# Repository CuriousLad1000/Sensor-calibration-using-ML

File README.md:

# Sensor calibration using Machine Learning

## Introduction

This repository presents one of the projects I built during the start of
the COVID-19 pandemic when there was a severe shortage of medical
equipment. Even something simple as a thermometer was either not
available or too costly to purchase. In this project, I used some
consumer-grade temperature sensors and calibrated them to provide
medical-grade precision and accuracy.

## Project Objective

The objective is to calibrate a commonly available temperature sensor to
provide medical grade accuracy. The sensor is calibrated by taking
readings from multiple medical grade thermometers as a benchmark and
then averaging them out.

The reading taken from thermometer and the sensor being calibrated are
then fit to a regression model to increase sensor's accuracy.

The model is then uploaded to the controller and after interfacing with
sensors and peripherals required, it produces accurate results under
calibrated range of a clinical thermometer (94-108 degrees F).

*Full list of features and capabilities are listed in a separate section below.*

## Hardware used

-   Arduino nano/pro min

-   3D printer casing for the temperature gun

-   Bright OLED display

-   battery

-   Laser pointer

-   Contactless Temperature sensor

-   Custom-built calibration heat bed

-   Clinical thermometers

-   Precision temperature sensors for heat-bed and reference

## Software used

-   Arduino IDE (C/C++ Programming)

-   Excel for data collection and regression model

-   GIMP for UI designing

-   Eagle for PCB designing

-   Fritzing for prototyping wiring diagram

## Features offered

-   Calibrated contactless temperature sensor.

-   Power-saving mode.

-   Inbuilt rechargeable batteries.

-   Temperature range similar to clinical thermometer.

-   Bright OLED display with easy-to-read readouts.

## Device pics

**Device**

<br/>

<br/>
<br/>

**Calibration setup <i>(gotta work with whatever you have during pandemic... this is a makeshift Heatbed PID controlled)</i>**

<br/>

<br/>
<br/>

<br/>

<br/>
<br/>

**Circuit board**

<br/>

<br/>
<br/>

**Calibration process**

<br/>

<br/>
<br/>

**UI Testing**

<br/>

<br/>
<br/>

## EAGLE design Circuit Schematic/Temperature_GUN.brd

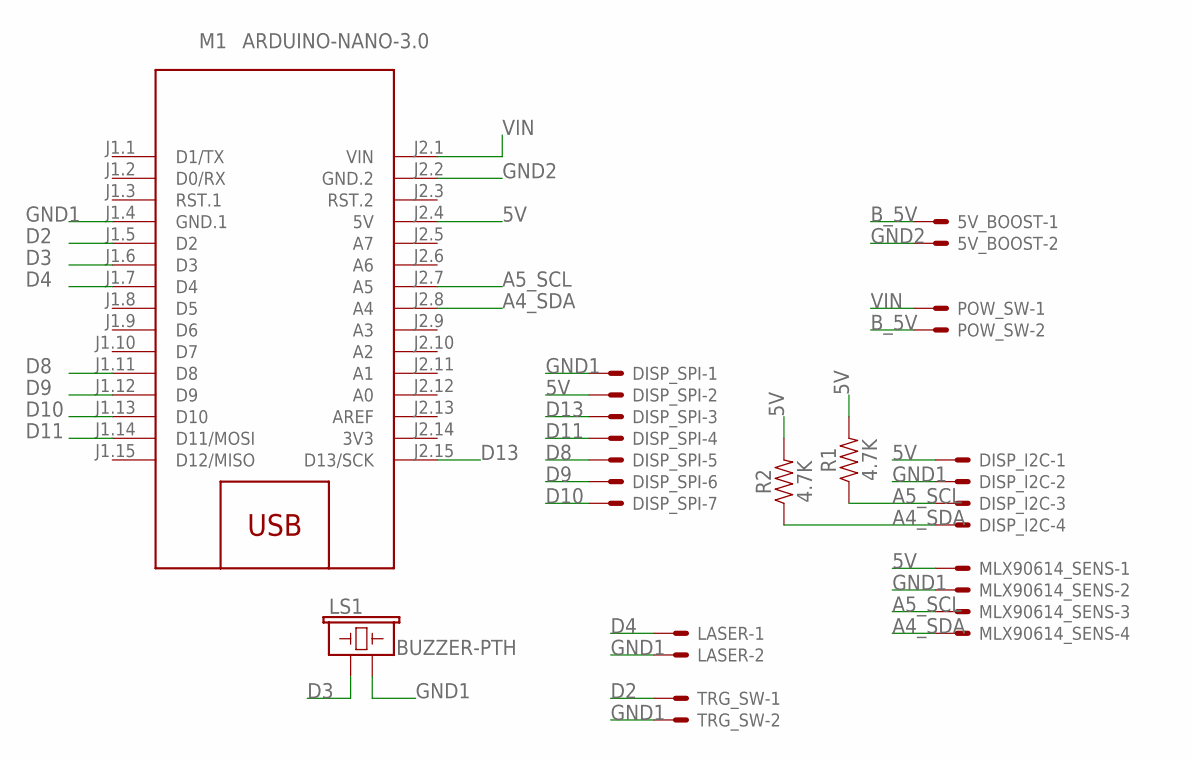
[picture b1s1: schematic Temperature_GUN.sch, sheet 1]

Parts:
5V_BOOST: JST-XH-02-PIN-ROUND-PAD; JST-XH-02-PACKAGE-ROUND-PAD
DISP_I2C: JST-XH-04-PIN-ROUND-PAD; JST-XH-04-PACKAGE-ROUND-PAD
DISP_SPI: JST-XH-07-PIN-ROUND-PAD; JST-XH-07-PACKAGE-ROUND-PAD
LASER: JST-XH-02-PIN-ROUND-PAD; JST-XH-02-PACKAGE-ROUND-PAD
LS1: BUZZER-PTH; BUZZER-12MM
M1: ARDUINO-NANO-3.0
MLX90614_SENS: JST-XH-04-PIN-ROUND-PAD; JST-XH-04-PACKAGE-ROUND-PAD
POW_SW: JST-XH-02-PIN-ROUND-PAD; JST-XH-02-PACKAGE-ROUND-PAD
R1, R2: 4.7K; AXIAL-0.3
TRG_SW: JST-XH-02-PIN-ROUND-PAD; JST-XH-02-PACKAGE-ROUND-PAD

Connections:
3V3: M1.J2.14 (3V3)
5V: DISP_I2C.1, DISP_SPI.2, M1.J2.4 (5V), MLX90614_SENS.1, R1.P$2 (2), R2.P$2 (2)
A4_SDA: DISP_I2C.4, M1.J2.8 (A4), MLX90614_SENS.4, R2.P$1 (1)
A5_SCL: DISP_I2C.3, M1.J2.7 (A5), MLX90614_SENS.3, R1.P$1 (1)
B_5V: 5V_BOOST.1, POW_SW.2
D2: M1.J1.5 (D2), TRG_SW.1
D3: LS1.+ (1), M1.J1.6 (D3)
D4: LASER.1, M1.J1.7 (D4)
D8: DISP_SPI.5, M1.J1.11 (D8)
D9: DISP_SPI.6, M1.J1.12 (D9)
D10: DISP_SPI.7, M1.J1.13 (D10)
D11: DISP_SPI.4, M1.J1.14 (D11/MOSI)
D13: DISP_SPI.3, M1.J2.15 (D13/SCK)
GND1: DISP_I2C.2, DISP_SPI.1, LASER.2, LS1.- (2), M1.J1.4 (GND.1), MLX90614_SENS.2, TRG_SW.2
GND2: 5V_BOOST.2, M1.J2.2 (GND.2)
VIN: M1.J2.1 (VIN), POW_SW.1

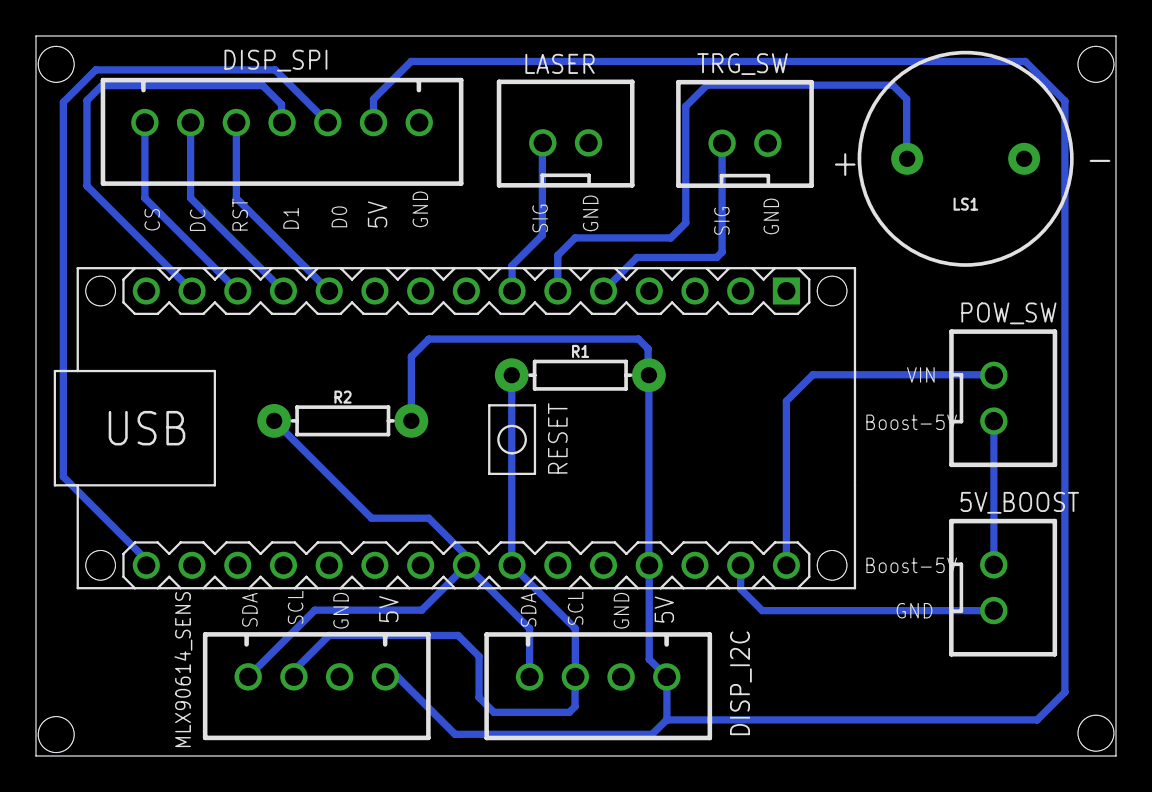
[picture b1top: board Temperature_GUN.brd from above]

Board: 2 copper layers, 60.0 x 40.0 mm, 11 parts (0 on the bottom side), 15 nets.

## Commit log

2022-06-26 Update 'README.md'
2022-06-26 Added code, cal. data, test_snips
    * added code
    * added Test code snips
    * added circuit board files
    * added wiring diagrams
    * added calibration data used in regression model.

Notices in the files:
parts and their libraries:
diy-modules: Released under the Creative Commons Attribution 4.0 International License: http://creativecommons.org/licenses/by/4.0
SparkFun-Electromechanical: Licensing: Creative Commons ShareAlike 4.0 International - https://creativecommons.org/licenses/by-sa/4.0
